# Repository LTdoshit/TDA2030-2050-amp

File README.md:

# TDA2030-2050-amp
its based on the schematic from ST

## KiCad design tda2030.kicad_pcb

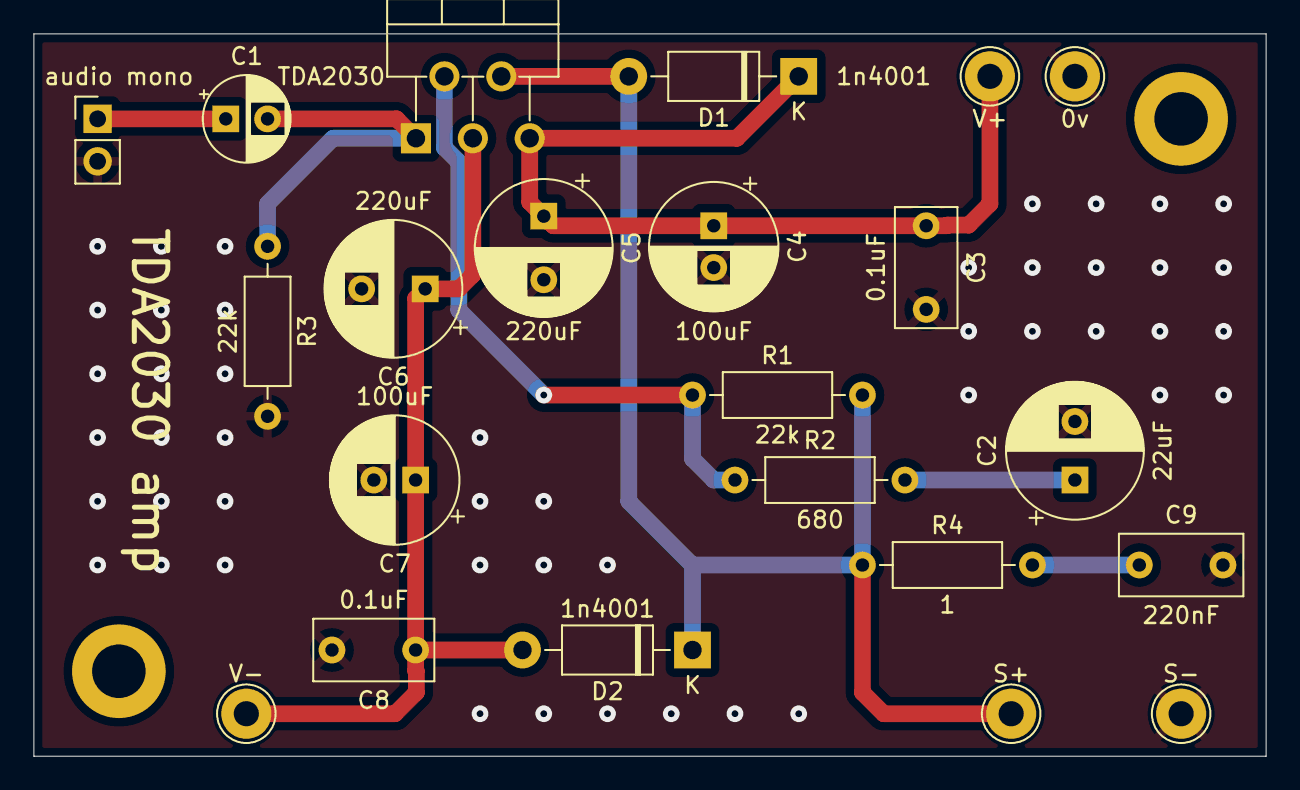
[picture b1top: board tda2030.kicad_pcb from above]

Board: 2 copper layers, 73.7 x 43.2 mm, 22 parts (0 on the bottom side), 9 nets.

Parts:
0v: TestPoint_THTPad_D3.0mm_Drill1.5mm
C1: 1uF; CP_Radial_D5.0mm_P2.50mm
C2: 22uF; CP_Radial_D8.0mm_P3.50mm
C3, C8: 0.1uF; C_Rect_L7.0mm_W3.5mm_P5.00mm
C4, C7: 100uF; CP_Radial_D7.5mm_P2.50mm
C5, C6: 220uF; CP_Radial_D8.0mm_P3.80mm
C9: 220nF; C_Rect_L7.2mm_W3.5mm_P5.00mm_FKS2_FKP2_MKS2_MKP2
D1, D2: 1n4001; D_DO-41_SOD81_P10.16mm_Horizontal
R1, R3: 22k; R_Axial_DIN0207_L6.3mm_D2.5mm_P10.16mm_Horizontal
R2: 680; R_Axial_DIN0207_L6.3mm_D2.5mm_P10.16mm_Horizontal
R4: 1; R_Axial_DIN0207_L6.3mm_D2.5mm_P10.16mm_Horizontal
S+: TestPoint_THTPad_D3.0mm_Drill1.5mm
S-: TestPoint_THTPad_D3.0mm_Drill1.5mm
U1: TDA2030; TO-220-5_P3.4x3.7mm_StaggerOdd_Lead3.8mm_Vertical
V+: TestPoint_THTPad_D3.0mm_Drill1.5mm
V-: TestPoint_THTPad_D3.0mm_Drill1.5mm
audio mono: PinHeader_1x02_P2.54mm_Vertical

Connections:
GND: 0v.1, C2.2, C3.2, C4.2, C5.2, C6.2, C7.2, C8.2, C9.2, R3.2, S-.1, audio mono.2
unnamed: C2.1, R2.2
unnamed: C9.1, R4.2
unnamed: C1.2, R3.1, U1.1 (+)
unnamed: R1.1, R2.1, U1.2 (-)
S+: D1.2 (A), D2.1 (K), R1.2, R4.1, S+.1, U1.4
V-: C6.1, C7.1, C8.1, D2.2 (A), U1.3 (-Vs), V-.1
audio in: C1.1, audio mono.1
v+: C3.1, C4.1, C5.1, D1.1 (K), U1.5 (+Vs), V+.1
